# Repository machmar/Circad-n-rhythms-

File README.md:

# Circad-n-rhythms-

Sadly, this project has stalled and while I have plans to make it much better in the future, there so far is no date for these plans and other stuff is more important right now.    
  
If you are just seeing this module for the first time, let me introduce you to the basic concept of what it is and what it was.  
This is a eurorack module that was originally a clone of *Circadian Rhythms* by *TipTop Audio* but later on I decided to make it my own. I have rewritten the code and redisegined the PCB for it multiple times but never got into a place were the programming would get clean and straight forward. I suspect this is mostly because I coded the whole thing in one file with Arduino IDE. So if any new versions of the code ever come out, it willl be written in Microchip Studio instead.  But the Hardware, other than the noise on powerlines that it makes, is a in a good state with all the stuff nescessary for further development  
  
Anyways, all the mistakes that I am aware are now fixed and the module should be usable and responsive. the DAC is not used so it is not nescessary but if you want to you can have a go at adding the functionality, the protocol should be implemented with functions for intialization, selecting a channel and setting the voltage.

If you want to build it, or even build multiple and sell it to other people, send me an e-mail (marekmach24@gmail.com) and I'll send you the files for 3D printing like the faceplate, buttons and others (I'll also tell you what the serial number should be 🤭🤭). Advantage for doing it this way is that if you face any issues, I can help you out pretty quickly and easilly as you already have a direct line to me.  

More info here:  
Flashing guide [Here on wiki](https://github.com/machmar/Circad-n-rhythms-/wiki/)  
Video overview [on my youtube channel](https://youtu.be/im8Ey7QF54s)

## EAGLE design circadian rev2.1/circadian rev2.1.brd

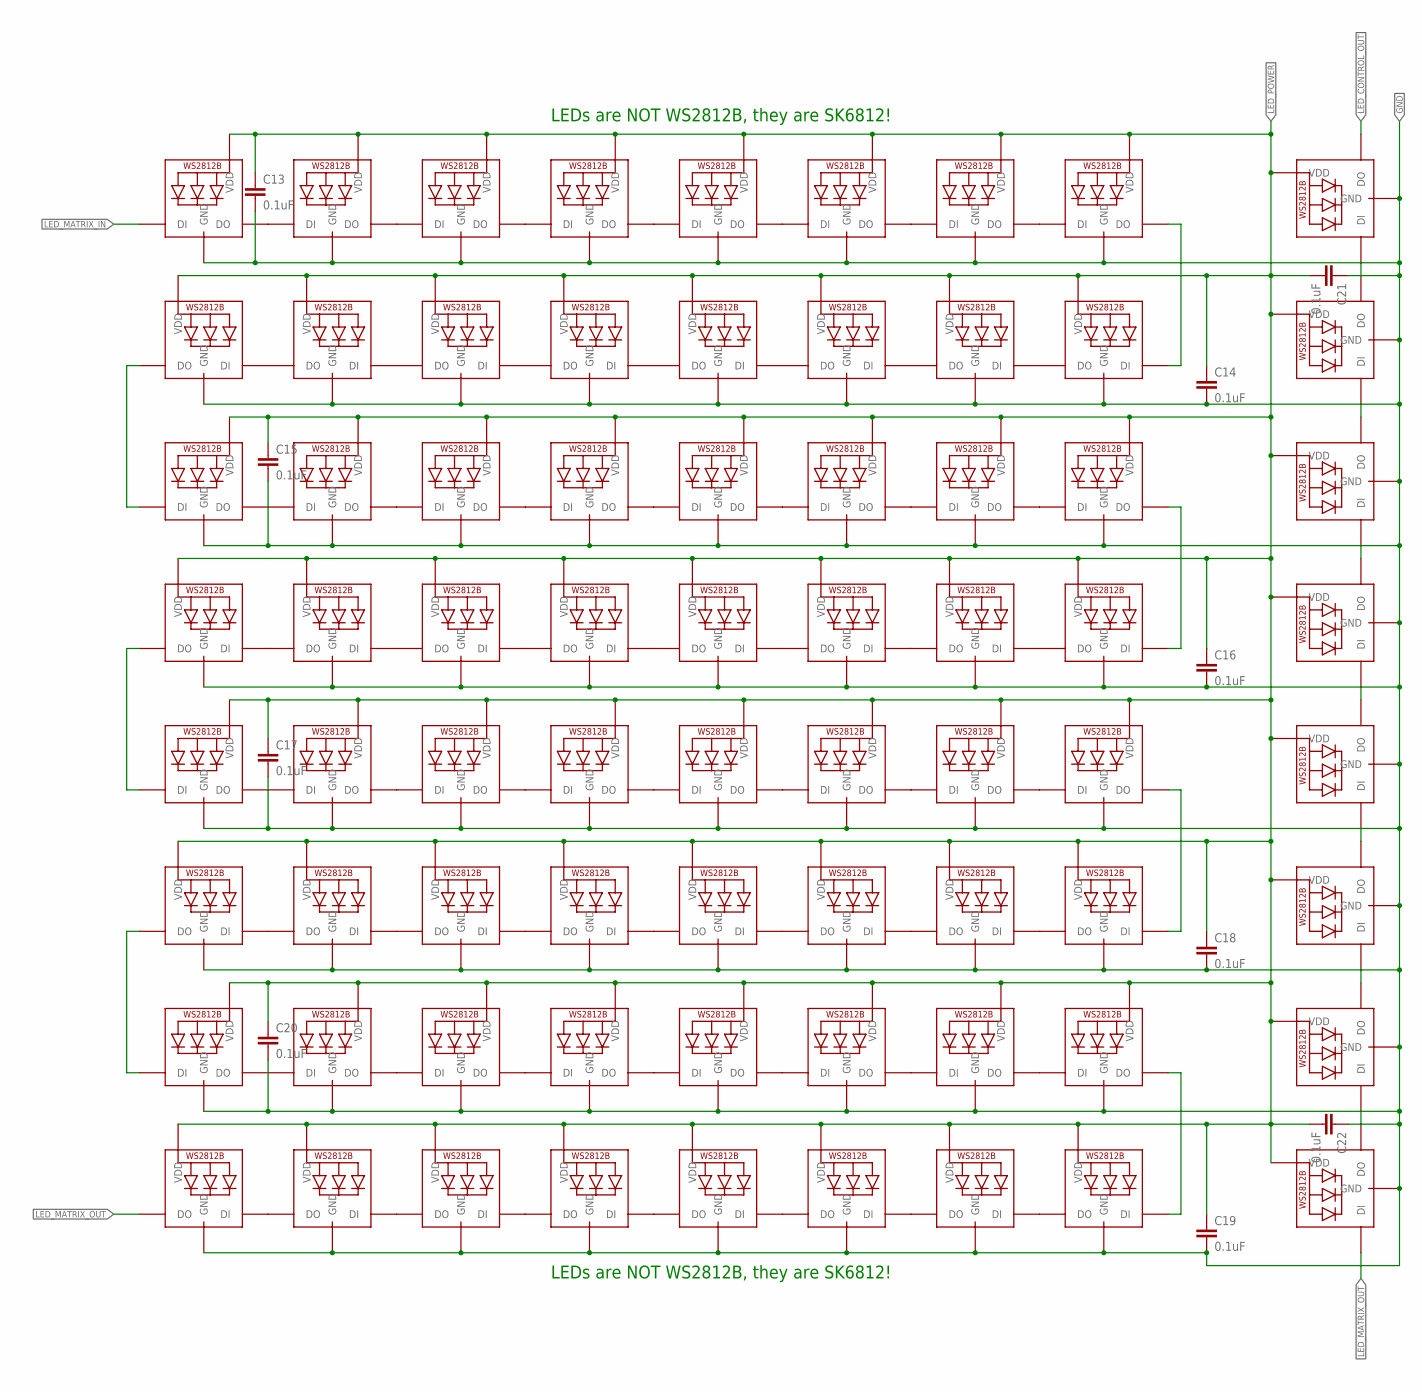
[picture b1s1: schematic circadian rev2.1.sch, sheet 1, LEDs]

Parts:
C13, C14, C15, C16, C17, C18, C19, C20, C21, C22: 0.1uF; 0603
LED1, LED2, LED3, LED4, LED5, LED6, LED7, LED8, LED9, LED10, LED11, LED12, LED13, LED14, LED15, LED16, LED17, LED18, LED19, LED20, LED21, LED22, LED23, LED24, LED25, LED26, LED27, LED28, LED29, LED30, LED31, LED32, LED33, LED34, LED35, LED36, LED37, LED38, LED39, LED40, LED41, LED42, LED43, LED44, LED45, LED46, LED47, LED48, LED49, LED50, LED51, LED52, LED53, LED54, LED55, LED56, LED57, LED58, LED59, LED60, LED61, LED62, LED63, LED64, LED65, LED66, LED67, LED68, LED69, LED70, LED71, LED72: SK68123535; LED3535

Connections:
GND: C13.2, C14.2, C15.2, C16.2, C17.2, C18.2, C19.2, C20.2, C21.1, C22.1, LED1.4 (GND), LED2.4 (GND), LED3.4 (GND), LED4.4 (GND), LED5.4 (GND), LED6.4 (GND), LED7.4 (GND), LED8.4 (GND), LED9.4 (GND), LED10.4 (GND), LED11.4 (GND), LED12.4 (GND), LED13.4 (GND), LED14.4 (GND), LED15.4 (GND), LED16.4 (GND), LED17.4 (GND), LED18.4 (GND), LED19.4 (GND), LED20.4 (GND), LED21.4 (GND), LED22.4 (GND), LED23.4 (GND), LED24.4 (GND), LED25.4 (GND), LED26.4 (GND), LED27.4 (GND), LED28.4 (GND), LED29.4 (GND), LED30.4 (GND), LED31.4 (GND), LED32.4 (GND), LED33.4 (GND), LED34.4 (GND), LED35.4 (GND), LED36.4 (GND), LED37.4 (GND), LED38.4 (GND), LED39.4 (GND), LED40.4 (GND), LED41.4 (GND), LED42.4 (GND), LED43.4 (GND), LED44.4 (GND), LED45.4 (GND), LED46.4 (GND), LED47.4 (GND), LED48.4 (GND), LED49.4 (GND), LED50.4 (GND), LED51.4 (GND), LED52.4 (GND), LED53.4 (GND), LED54.4 (GND), LED55.4 (GND), LED56.4 (GND), LED57.4 (GND), LED58.4 (GND), LED59.4 (GND), LED60.4 (GND), LED61.4 (GND), LED62.4 (GND), LED63.4 (GND), LED64.4 (GND), LED65.4 (GND), LED66.4 (GND), LED67.4 (GND), LED68.4 (GND), LED69.4 (GND), LED70.4 (GND), LED71.4 (GND), LED72.4 (GND); also elsewhere on the board
LED_CONTROL_OUT: LED65.3 (DO)
LED_MATRIX_IN: LED1.1 (DI); also elsewhere on the board
LED_MATRIX_OUT: LED64.3 (DO), LED72.1 (DI)
LED_POWER: C13.1, C14.1, C15.1, C16.1, C17.1, C18.1, C19.1, C20.1, C21.2, C22.2, LED1.2 (VDD), LED2.2 (VDD), LED3.2 (VDD), LED4.2 (VDD), LED5.2 (VDD), LED6.2 (VDD), LED7.2 (VDD), LED8.2 (VDD), LED9.2 (VDD), LED10.2 (VDD), LED11.2 (VDD), LED12.2 (VDD), LED13.2 (VDD), LED14.2 (VDD), LED15.2 (VDD), LED16.2 (VDD), LED17.2 (VDD), LED18.2 (VDD), LED19.2 (VDD), LED20.2 (VDD), LED21.2 (VDD), LED22.2 (VDD), LED23.2 (VDD), LED24.2 (VDD), LED25.2 (VDD), LED26.2 (VDD), LED27.2 (VDD), LED28.2 (VDD), LED29.2 (VDD), LED30.2 (VDD), LED31.2 (VDD), LED32.2 (VDD), LED33.2 (VDD), LED34.2 (VDD), LED35.2 (VDD), LED36.2 (VDD), LED37.2 (VDD), LED38.2 (VDD), LED39.2 (VDD), LED40.2 (VDD), LED41.2 (VDD), LED42.2 (VDD), LED43.2 (VDD), LED44.2 (VDD), LED45.2 (VDD), LED46.2 (VDD), LED47.2 (VDD), LED48.2 (VDD), LED49.2 (VDD), LED50.2 (VDD), LED51.2 (VDD), LED52.2 (VDD), LED53.2 (VDD), LED54.2 (VDD), LED55.2 (VDD), LED56.2 (VDD), LED57.2 (VDD), LED58.2 (VDD), LED59.2 (VDD), LED60.2 (VDD), LED61.2 (VDD), LED62.2 (VDD), LED63.2 (VDD), LED64.2 (VDD), LED65.2 (VDD), LED66.2 (VDD), LED67.2 (VDD), LED68.2 (VDD), LED69.2 (VDD), LED70.2 (VDD), LED71.2 (VDD), LED72.2 (VDD); also elsewhere on the board
unnamed: LED9.3 (DO), LED10.1 (DI)
unnamed: LED10.3 (DO), LED11.1 (DI)
unnamed: LED11.3 (DO), LED12.1 (DI)
unnamed: LED12.3 (DO), LED13.1 (DI)
unnamed: LED13.3 (DO), LED14.1 (DI)
unnamed: LED14.3 (DO), LED15.1 (DI)
unnamed: LED15.3 (DO), LED16.1 (DI)
unnamed: LED8.3 (DO), LED9.1 (DI)
unnamed: LED17.3 (DO), LED18.1 (DI)
unnamed: LED18.3 (DO), LED19.1 (DI)
unnamed: LED19.3 (DO), LED20.1 (DI)
unnamed: LED20.3 (DO), LED21.1 (DI)
unnamed: LED21.3 (DO), LED22.1 (DI)
unnamed: LED22.3 (DO), LED23.1 (DI)
unnamed: LED23.3 (DO), LED24.1 (DI)
unnamed: LED1.3 (DO), LED2.1 (DI)
unnamed: LED2.3 (DO), LED3.1 (DI)
unnamed: LED3.3 (DO), LED4.1 (DI)
unnamed: LED4.3 (DO), LED5.1 (DI)
unnamed: LED5.3 (DO), LED6.1 (DI)
unnamed: LED6.3 (DO), LED7.1 (DI)
unnamed: LED7.3 (DO), LED8.1 (DI)
unnamed: LED25.3 (DO), LED26.1 (DI)
unnamed: LED26.3 (DO), LED27.1 (DI)
unnamed: LED27.3 (DO), LED28.1 (DI)
unnamed: LED28.3 (DO), LED29.1 (DI)
unnamed: LED29.3 (DO), LED30.1 (DI)
unnamed: LED30.3 (DO), LED31.1 (DI)
unnamed: LED31.3 (DO), LED32.1 (DI)
unnamed: LED24.3 (DO), LED25.1 (DI)
unnamed: LED33.3 (DO), LED34.1 (DI)
unnamed: LED34.3 (DO), LED35.1 (DI)
unnamed: LED35.3 (DO), LED36.1 (DI)
unnamed: LED36.3 (DO), LED37.1 (DI)
unnamed: LED37.3 (DO), LED38.1 (DI)
unnamed: LED38.3 (DO), LED39.1 (DI)
unnamed: LED39.3 (DO), LED40.1 (DI)
unnamed: LED41.3 (DO), LED42.1 (DI)
unnamed: LED42.3 (DO), LED43.1 (DI)
unnamed: LED43.3 (DO), LED44.1 (DI)
unnamed: LED44.3 (DO), LED45.1 (DI)
unnamed: LED45.3 (DO), LED46.1 (DI)
unnamed: LED46.3 (DO), LED47.1 (DI)
unnamed: LED47.3 (DO), LED48.1 (DI)
unnamed: LED40.3 (DO), LED41.1 (DI)
unnamed: LED49.3 (DO), LED50.1 (DI)
unnamed: LED50.3 (DO), LED51.1 (DI)
unnamed: LED51.3 (DO), LED52.1 (DI)
unnamed: LED52.3 (DO), LED53.1 (DI)
unnamed: LED53.3 (DO), LED54.1 (DI)
unnamed: LED54.3 (DO), LED55.1 (DI)
unnamed: LED55.3 (DO), LED56.1 (DI)
unnamed: LED57.3 (DO), LED58.1 (DI)
unnamed: LED58.3 (DO), LED59.1 (DI)
unnamed: LED59.3 (DO), LED60.1 (DI)
unnamed: LED60.3 (DO), LED61.1 (DI)
unnamed: LED61.3 (DO), LED62.1 (DI)
unnamed: LED62.3 (DO), LED63.1 (DI)
unnamed: LED63.3 (DO), LED64.1 (DI)
unnamed: LED56.3 (DO), LED57.1 (DI)
unnamed: LED16.3 (DO), LED17.1 (DI)
unnamed: LED32.3 (DO), LED33.1 (DI)
unnamed: LED48.3 (DO), LED49.1 (DI)
unnamed: LED66.1 (DI), LED67.3 (DO)
unnamed: LED67.1 (DI), LED68.3 (DO)
unnamed: LED68.1 (DI), LED69.3 (DO)
unnamed: LED69.1 (DI), LED70.3 (DO)
unnamed: LED70.1 (DI), LED71.3 (DO)
unnamed: LED71.1 (DI), LED72.3 (DO)
unnamed: LED65.1 (DI), LED66.3 (DO)

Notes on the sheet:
LEDs are NOT WS2812B, they are SK6812!

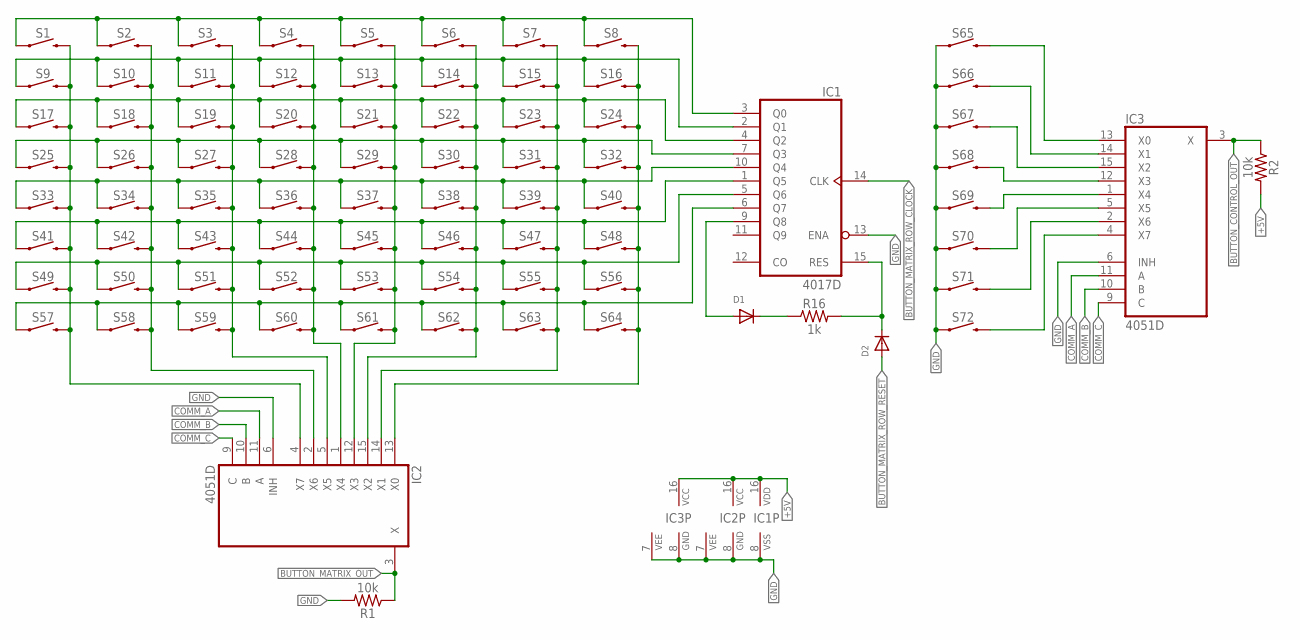
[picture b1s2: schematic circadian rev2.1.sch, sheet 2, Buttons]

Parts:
D1, D2: DIODESOD-123; SOD-123
IC1: 4017D; SO16
IC2, IC3: 4051D; SO16
R1, R2: 10k; 0603
R16: 1k; 0603
S1, S2, S3, S4, S5, S6, S7, S8, S9, S10, S11, S12, S13, S14, S15, S16, S17, S18, S19, S20, S21, S22, S23, S24, S25, S26, S27, S28, S29, S30, S31, S32, S33, S34, S35, S36, S37, S38, S39, S40, S41, S42, S43, S44, S45, S46, S47, S48, S49, S50, S51, S52, S53, S54, S55, S56, S57, S58, S59, S60, S61, S62, S63, S64, S65, S66, S67, S68, S69, S70, S71, S72: MOMENTARY-SWITCH-SPST-SMD-6.0X3.5MM; TACTILE_SWITCH_SMD_6.0X3.5MM

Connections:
+5V: IC1.16 (VDD), IC2.16 (VCC), IC3.16 (VCC), R2.2; also elsewhere on the board
BUTTON_CONTROL_OUT: IC3.3 (X), R2.1; also elsewhere on the board
BUTTON_MATRIX_COLLUM1: IC2.4 (X7), S1.2, S9.2, S17.2, S25.2, S33.2, S41.2, S49.2, S57.2
BUTTON_MATRIX_COLLUM2: IC2.2 (X6), S2.2, S10.2, S18.2, S26.2, S34.2, S42.2, S50.2, S58.2
BUTTON_MATRIX_COLLUM3: IC2.5 (X5), S3.2, S11.2, S19.2, S27.2, S35.2, S43.2, S51.2, S59.2
BUTTON_MATRIX_COLLUM4: IC2.1 (X4), S4.2, S12.2, S20.2, S28.2, S36.2, S44.2, S52.2, S60.2
BUTTON_MATRIX_COLLUM5: IC2.12 (X3), S5.2, S13.2, S21.2, S29.2, S37.2, S45.2, S53.2, S61.2
BUTTON_MATRIX_COLLUM6: IC2.15 (X2), S6.2, S14.2, S22.2, S30.2, S38.2, S46.2, S54.2, S62.2
BUTTON_MATRIX_COLLUM7: IC2.14 (X1), S7.2, S15.2, S23.2, S31.2, S39.2, S47.2, S55.2, S63.2
BUTTON_MATRIX_COLLUM8: IC2.13 (X0), S8.2, S16.2, S24.2, S32.2, S40.2, S48.2, S56.2, S64.2
BUTTON_MATRIX_OUT: IC2.3 (X), R1.1; also elsewhere on the board
BUTTON_MATRIX_ROW1: IC1.3 (Q0), S1.1, S2.1, S3.1, S4.1, S5.1, S6.1, S7.1, S8.1
BUTTON_MATRIX_ROW2: IC1.2 (Q1), S9.1, S10.1, S11.1, S12.1, S13.1, S14.1, S15.1, S16.1
BUTTON_MATRIX_ROW3: IC1.4 (Q2), S17.1, S18.1, S19.1, S20.1, S21.1, S22.1, S23.1, S24.1
BUTTON_MATRIX_ROW4: IC1.7 (Q3), S25.1, S26.1, S27.1, S28.1, S29.1, S30.1, S31.1, S32.1
BUTTON_MATRIX_ROW5: IC1.10 (Q4), S33.1, S34.1, S35.1, S36.1, S37.1, S38.1, S39.1, S40.1
BUTTON_MATRIX_ROW6: IC1.1 (Q5), S41.1, S42.1, S43.1, S44.1, S45.1, S46.1, S47.1, S48.1
BUTTON_MATRIX_ROW7: IC1.5 (Q6), S49.1, S50.1, S51.1, S52.1, S53.1, S54.1, S55.1, S56.1
BUTTON_MATRIX_ROW8: IC1.6 (Q7), S57.1, S58.1, S59.1, S60.1, S61.1, S62.1, S63.1, S64.1
BUTTON_MATRIX_ROW_CLOCK: IC1.14 (CLK); also elsewhere on the board
BUTTON_MATRIX_ROW_RESET: D2.A; also elsewhere on the board
COMM_A: IC2.11 (A), IC3.11 (A); also elsewhere on the board
COMM_B: IC2.10 (B), IC3.10 (B); also elsewhere on the board
COMM_C: IC2.9 (C), IC3.9 (C); also elsewhere on the board
GND: IC1.8 (VSS), IC1.13 (ENA), IC2.6 (INH), IC2.7 (VEE), IC2.8 (GND), IC3.6 (INH), IC3.7 (VEE), IC3.8 (GND), R1.2, S65.1, S66.1, S67.1, S68.1, S69.1, S70.1, S71.1, S72.1; also elsewhere on the board
unnamed: IC3.12 (X3), S68.2
unnamed: IC3.1 (X4), S69.2
unnamed: IC3.5 (X5), S70.2
unnamed: IC3.15 (X2), S67.2
unnamed: IC3.14 (X1), S66.2
unnamed: IC3.13 (X0), S65.2
unnamed: IC3.2 (X6), S71.2
unnamed: IC3.4 (X7), S72.2
unnamed: D1.C, R16.1
unnamed: D1.A, IC1.9 (Q8)
unnamed: D2.C, IC1.15 (RES), R16.2

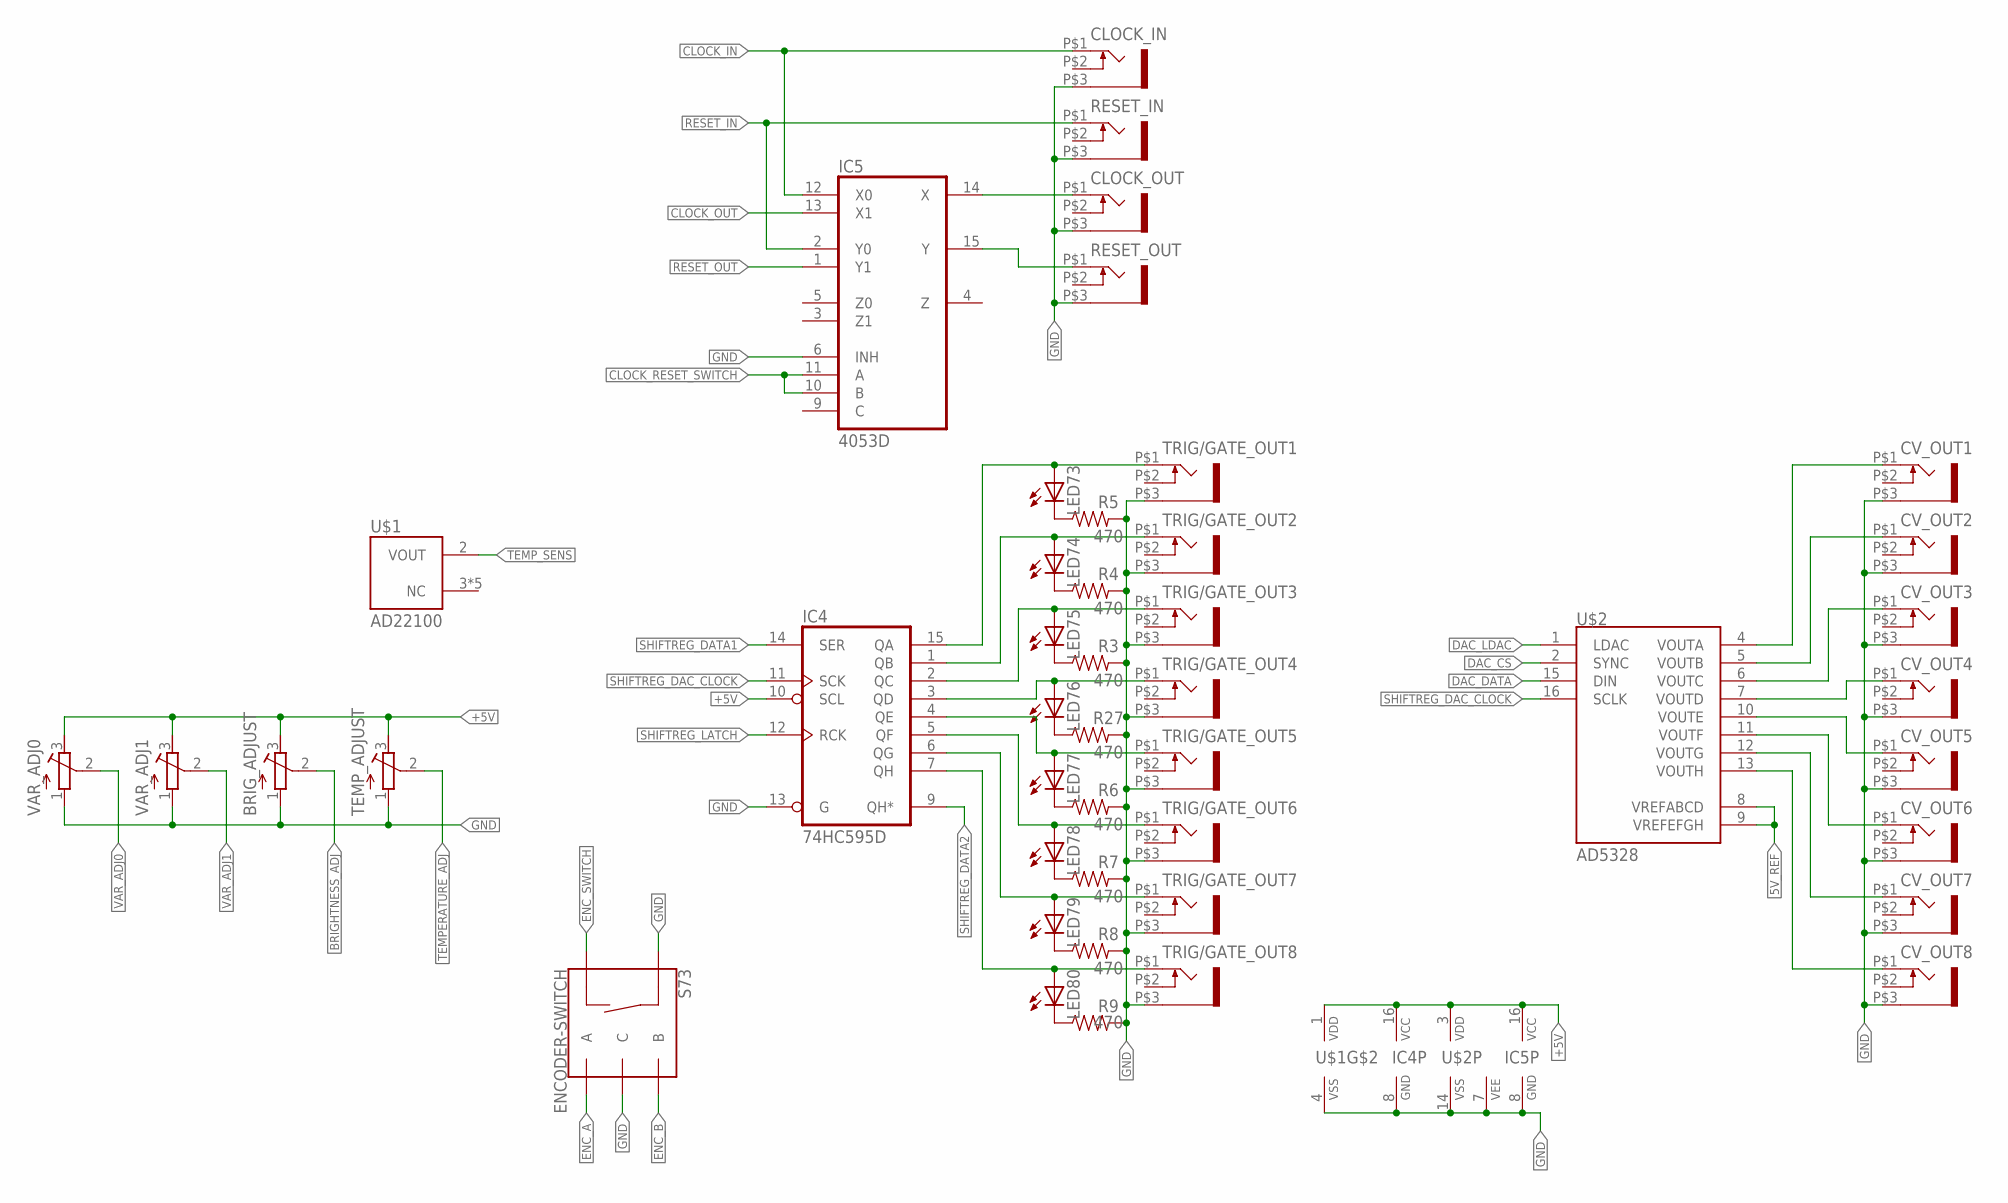
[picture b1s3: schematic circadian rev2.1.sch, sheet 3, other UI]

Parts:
BRIG_ADJUST: R-TRIMM4G/J; RTRIM4G/J
CLOCK_IN: WQP-PJ301M-12_JACK
CLOCK_OUT: WQP-PJ301M-12_JACK
CV_OUT1, CV_OUT2, CV_OUT3, CV_OUT4, CV_OUT5, CV_OUT6, CV_OUT7, CV_OUT8: WQP-PJ301M-12_JACK
IC4: 74HC595D; SO16
IC5: 4053D; SO16
LED73, LED74, LED75, LED76, LED77, LED78, LED79, LED80: LED5MM
R3, R4, R5, R6, R7, R8, R9, R27: 470; 0603
RESET_IN: WQP-PJ301M-12_JACK
RESET_OUT: WQP-PJ301M-12_JACK
S73: ENCODER-SWITCH; ROTARY_ENC_PLAIN
TEMP_ADJUST: R-TRIMM4G/J; RTRIM4G/J
TRIG/GATE_OUT1, TRIG/GATE_OUT2, TRIG/GATE_OUT3, TRIG/GATE_OUT4, TRIG/GATE_OUT5, TRIG/GATE_OUT6, TRIG/GATE_OUT7, TRIG/GATE_OUT8: WQP-PJ301M-12_JACK
U$1: AD22100; SO08
U$2: AD5328; TSSOP-16
VAR_ADJ0, VAR_ADJ1: R-TRIMM4G/J; RTRIM4G/J

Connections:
5V_REF: U$2.8 (VREFABCD), U$2.9 (VREFEFGH); also elsewhere on the board
+5V: BRIG_ADJUST.3 (E), IC4.10 (SCL), IC4.16 (VCC), IC5.16 (VCC), TEMP_ADJUST.3 (E), U$1.1 (VDD), U$2.3 (VDD), VAR_ADJ0.3 (E), VAR_ADJ1.3 (E); also elsewhere on the board
BRIGHTNESS_ADJ: BRIG_ADJUST.2 (S); also elsewhere on the board
CLOCK_IN: CLOCK_IN.P$1 (2), IC5.12 (X0); also elsewhere on the board
CLOCK_OUT: IC5.13 (X1); also elsewhere on the board
CLOCK_RESET_SWITCH: IC5.10 (B), IC5.11 (A); also elsewhere on the board
DAC_CS: U$2.2 (SYNC); also elsewhere on the board
DAC_DATA: U$2.15 (DIN); also elsewhere on the board
DAC_LDAC: U$2.1 (LDAC); also elsewhere on the board
ENC_A: S73.A; also elsewhere on the board
ENC_B: S73.B; also elsewhere on the board
ENC_SWITCH: S73.SW-; also elsewhere on the board
GND: BRIG_ADJUST.1 (A), CLOCK_IN.P$3 (1), CLOCK_OUT.P$3 (1), CV_OUT1.P$3 (1), CV_OUT2.P$3 (1), CV_OUT3.P$3 (1), CV_OUT4.P$3 (1), CV_OUT5.P$3 (1), CV_OUT6.P$3 (1), CV_OUT7.P$3 (1), CV_OUT8.P$3 (1), IC4.8 (GND), IC4.13 (G), IC5.6 (INH), IC5.7 (VEE), IC5.8 (GND), R3.2, R4.2, R5.2, R6.2, R7.2, R8.2, R9.2, R27.2, RESET_IN.P$3 (1), RESET_OUT.P$3 (1), S73.C, S73.SW+, TEMP_ADJUST.1 (A), TRIG/GATE_OUT1.P$3 (1), TRIG/GATE_OUT2.P$3 (1), TRIG/GATE_OUT3.P$3 (1), TRIG/GATE_OUT4.P$3 (1), TRIG/GATE_OUT5.P$3 (1), TRIG/GATE_OUT6.P$3 (1), TRIG/GATE_OUT7.P$3 (1), TRIG/GATE_OUT8.P$3 (1), U$1.4 (VSS), U$2.14 (VSS), VAR_ADJ0.1 (A), VAR_ADJ1.1 (A); also elsewhere on the board
unnamed: IC4.4 (QE), LED77.A, TRIG/GATE_OUT5.P$1 (2)
unnamed: IC4.3 (QD), LED76.A, TRIG/GATE_OUT4.P$1 (2)
unnamed: IC4.5 (QF), LED78.A, TRIG/GATE_OUT6.P$1 (2)
unnamed: IC4.6 (QG), LED79.A, TRIG/GATE_OUT7.P$1 (2)
unnamed: IC4.7 (QH), LED80.A, TRIG/GATE_OUT8.P$1 (2)
unnamed: IC4.2 (QC), LED75.A, TRIG/GATE_OUT3.P$1 (2)
unnamed: IC4.1 (QB), LED74.A, TRIG/GATE_OUT2.P$1 (2)
unnamed: IC4.15 (QA), LED73.A, TRIG/GATE_OUT1.P$1 (2)
unnamed: CV_OUT4.P$1 (2), U$2.7 (VOUTD)
unnamed: CV_OUT5.P$1 (2), U$2.10 (VOUTE)
unnamed: CV_OUT6.P$1 (2), U$2.11 (VOUTF)
unnamed: CV_OUT7.P$1 (2), U$2.12 (VOUTG)
unnamed: CV_OUT8.P$1 (2), U$2.13 (VOUTH)
unnamed: CV_OUT3.P$1 (2), U$2.6 (VOUTC)
unnamed: CV_OUT2.P$1 (2), U$2.5 (VOUTB)
unnamed: CV_OUT1.P$1 (2), U$2.4 (VOUTA)
unnamed: CLOCK_OUT.P$1 (2), IC5.14 (X)
unnamed: IC5.15 (Y), RESET_OUT.P$1 (2)
unnamed: LED76.K (C), R27.1
unnamed: LED75.K (C), R3.1
unnamed: LED74.K (C), R4.1
unnamed: LED73.K (C), R5.1
unnamed: LED77.K (C), R6.1
unnamed: LED78.K (C), R7.1
unnamed: LED79.K (C), R8.1
unnamed: LED80.K (C), R9.1
RESET_IN: IC5.2 (Y0), RESET_IN.P$1 (2); also elsewhere on the board
RESET_OUT: IC5.1 (Y1); also elsewhere on the board
SHIFTREG_DAC_CLOCK: IC4.11 (SCK), U$2.16 (SCLK); also elsewhere on the board
SHIFTREG_DATA1: IC4.14 (SER); also elsewhere on the board
SHIFTREG_DATA2: IC4.9 (QH*)
SHIFTREG_LATCH: IC4.12 (RCK); also elsewhere on the board
TEMPERATURE_ADJ: TEMP_ADJUST.2 (S); also elsewhere on the board
TEMP_SENS: U$1.2 (VOUT); also elsewhere on the board
VAR_ADJ0: VAR_ADJ0.2 (S); also elsewhere on the board
VAR_ADJ1: VAR_ADJ1.2 (S); also elsewhere on the board

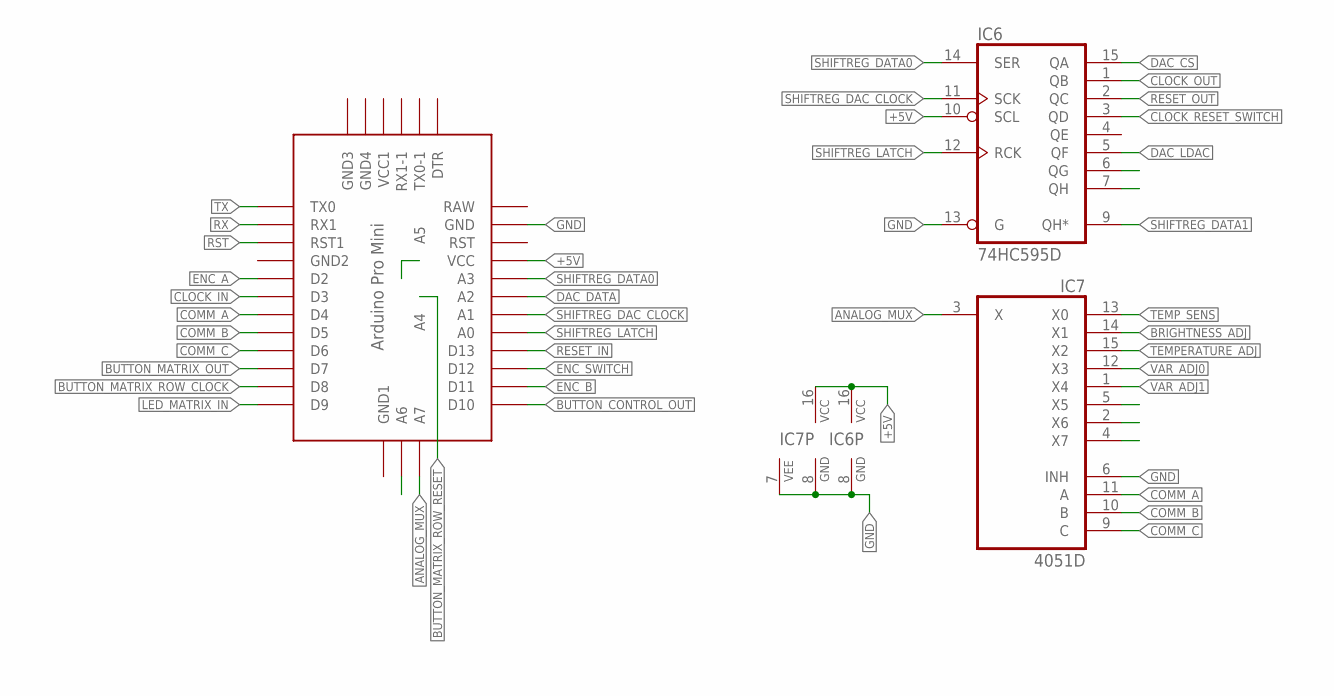
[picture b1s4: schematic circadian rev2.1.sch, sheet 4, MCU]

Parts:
IC6: 74HC595D; SO16
IC7: 4051D; SO16
U$3: ABK-PRO-MINI

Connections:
+5V: IC6.10 (SCL), IC6.16 (VCC), IC7.16 (VCC), U$3.VCC; also elsewhere on the board
ANALOG_MUX: IC7.3 (X), U$3.A7
BRIGHTNESS_ADJ: IC7.14 (X1); also elsewhere on the board
BUTTON_CONTROL_OUT: U$3.D10; also elsewhere on the board
BUTTON_MATRIX_OUT: U$3.D7; also elsewhere on the board
BUTTON_MATRIX_ROW_CLOCK: U$3.D8; also elsewhere on the board
BUTTON_MATRIX_ROW_RESET: U$3.A4; also elsewhere on the board
CLOCK_IN: U$3.D3; also elsewhere on the board
CLOCK_OUT: IC6.1 (QB); also elsewhere on the board
CLOCK_RESET_SWITCH: IC6.3 (QD); also elsewhere on the board
COMM_A: IC7.11 (A), U$3.D4; also elsewhere on the board
COMM_B: IC7.10 (B), U$3.D5; also elsewhere on the board
COMM_C: IC7.9 (C), U$3.D6; also elsewhere on the board
DAC_CS: IC6.15 (QA); also elsewhere on the board
DAC_DATA: U$3.A2; also elsewhere on the board
DAC_LDAC: IC6.5 (QF); also elsewhere on the board
ENC_A: U$3.D2; also elsewhere on the board
ENC_B: U$3.D11; also elsewhere on the board
ENC_SWITCH: U$3.D12; also elsewhere on the board
GND: IC6.8 (GND), IC6.13 (G), IC7.6 (INH), IC7.7 (VEE), IC7.8 (GND), U$3.GND; also elsewhere on the board
LED_MATRIX_IN: U$3.D9; also elsewhere on the board
RESET_IN: U$3.D13; also elsewhere on the board
RESET_OUT: IC6.2 (QC); also elsewhere on the board
RST: U$3.RST1; also elsewhere on the board
RX: U$3.RX1; also elsewhere on the board
SHIFTREG_DAC_CLOCK: IC6.11 (SCK), U$3.A1; also elsewhere on the board
SHIFTREG_DATA0: IC6.14 (SER), U$3.A3
SHIFTREG_DATA1: IC6.9 (QH*); also elsewhere on the board
SHIFTREG_LATCH: IC6.12 (RCK), U$3.A0; also elsewhere on the board
TEMPERATURE_ADJ: IC7.15 (X2); also elsewhere on the board
TEMP_SENS: IC7.13 (X0); also elsewhere on the board
TX: U$3.TX0; also elsewhere on the board
VAR_ADJ0: IC7.12 (X3); also elsewhere on the board
VAR_ADJ1: IC7.1 (X4); also elsewhere on the board

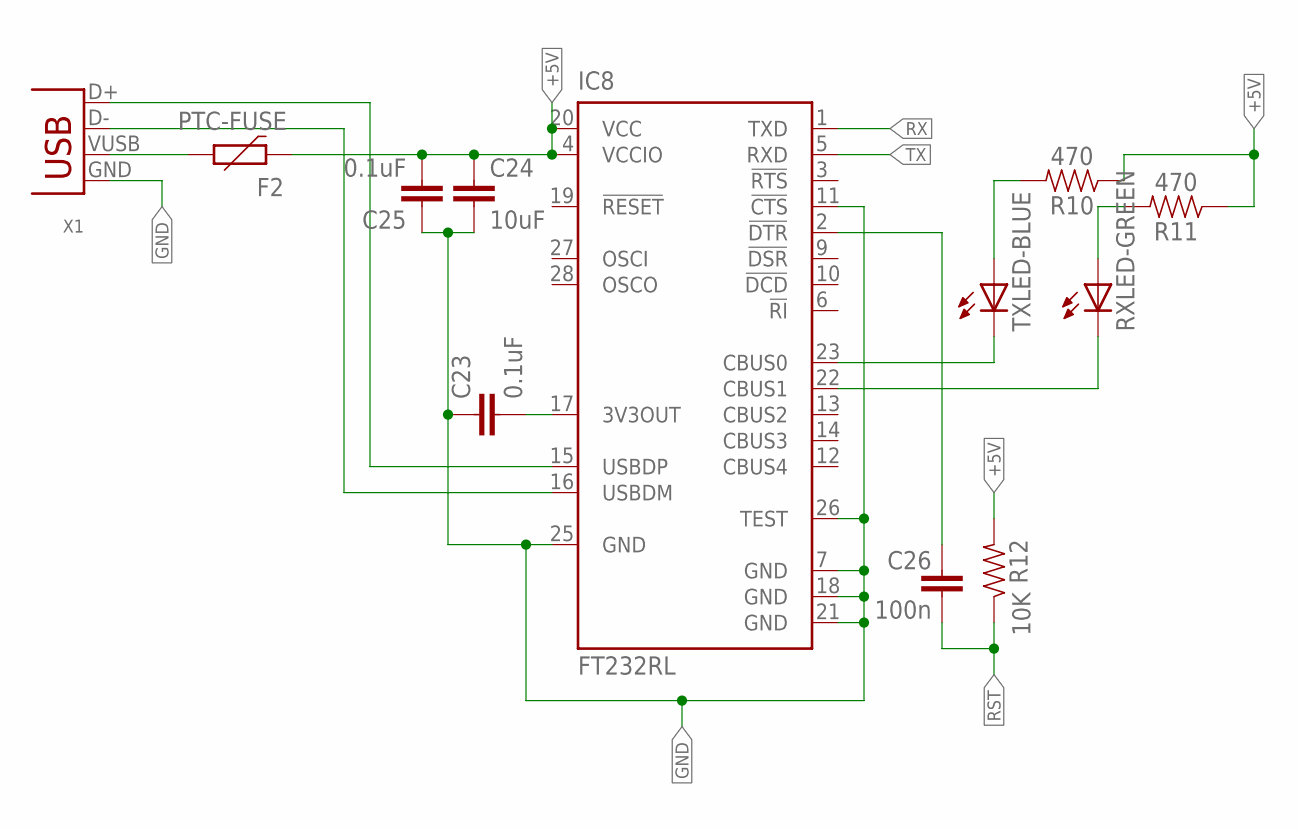
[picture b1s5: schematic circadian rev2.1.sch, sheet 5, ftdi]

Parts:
C23, C25: 0.1uF; 0603
C24: 10uF; 0603
C26: 100n; 0603-CAP
F2: PTC-FUSE; 1206
IC8: FT232RL; SSOP28
R10, R11: 470; 0603
R12: 10K; 0603-RES
RXLED-GREEN: LEDCHIP-LED0603; CHIP-LED0603
TXLED-BLUE: LEDCHIP-LED0603; CHIP-LED0603
X1: USB-B-S; USB-B-SMT

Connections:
+5V: C24.1, C25.2, F2.1, IC8.4 (VCCIO), IC8.20 (VCC), R10.1, R11.1, R12.2; also elsewhere on the board
DTR: C26.2, IC8.2 (!DTR)
GND: C23.1, C24.2, C25.1, IC8.7 (GND), IC8.11 (!CTS), IC8.18 (GND), IC8.21 (GND), IC8.25 (GND), IC8.26 (TEST), X1.GND; also elsewhere on the board
unnamed: R10.2, TXLED-BLUE.A
unnamed: R11.2, RXLED-GREEN.A
unnamed: IC8.23 (CBUS0), TXLED-BLUE.C
unnamed: IC8.22 (CBUS1), RXLED-GREEN.C
unnamed: F2.2, X1.VUSB (VBUS)
unnamed: IC8.15 (USBDP), X1.D+
unnamed: IC8.16 (USBDM), X1.D-
unnamed: C23.2, IC8.17 (3V3OUT)
RST: C26.1, R12.1; also elsewhere on the board
RX: IC8.1 (TXD); also elsewhere on the board
TX: IC8.5 (RXD); also elsewhere on the board

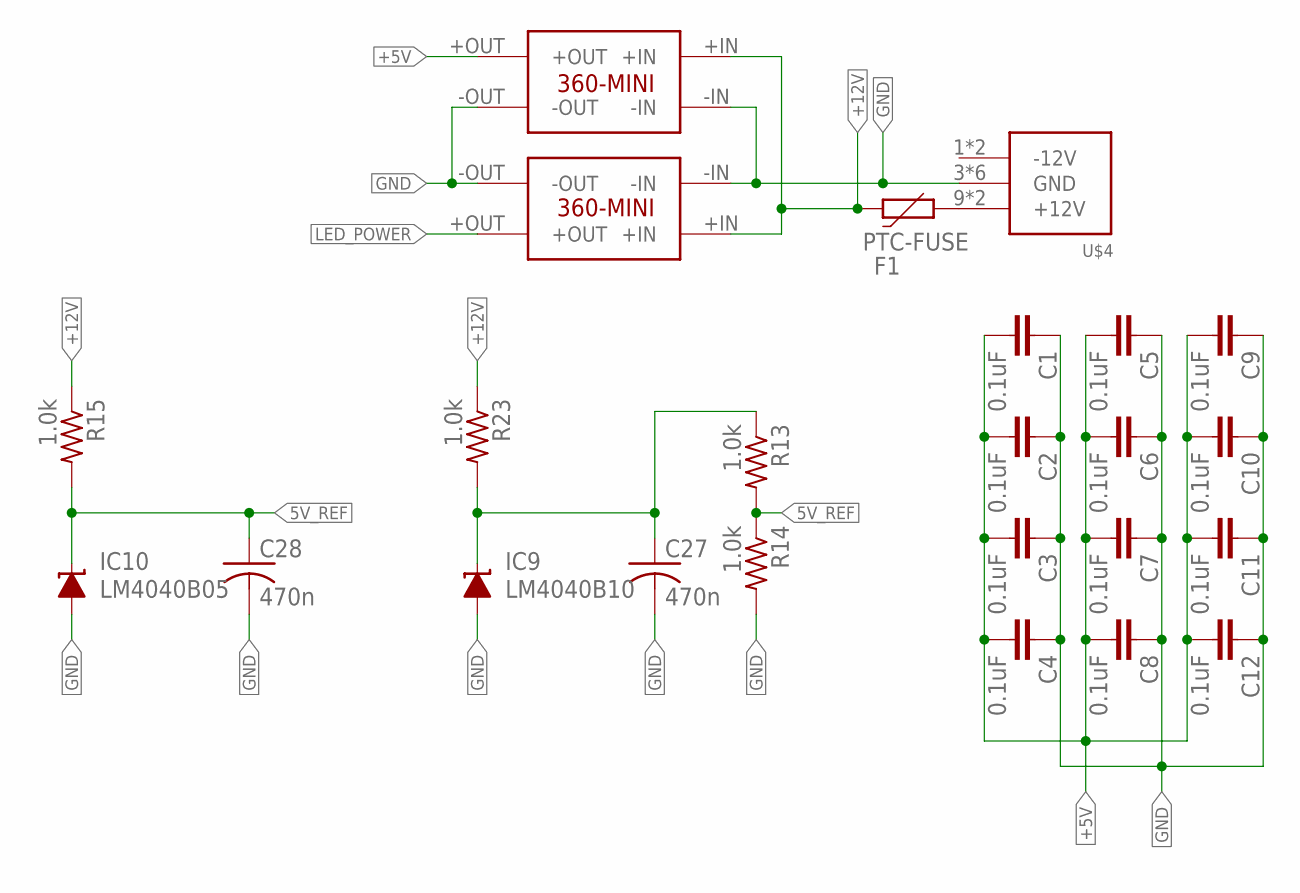
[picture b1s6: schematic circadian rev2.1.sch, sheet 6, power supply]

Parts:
C1, C2, C3, C4, C5, C6, C7, C8, C9, C10, C11, C12: 0.1uF; 0603
C27, C28: 470n; C0603
F1: PTC-FUSE; 1206
IC9: LM4040B10; DBZ_R-PDSO-G3
IC10: LM4040B05; DBZ_R-PDSO-G3
R13, R14, R15, R23: 1.0k; R0603
U$4: POWER_SIMPLE10; POWER_10
U$5, U$6: MINI-360SMD

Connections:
5V_REF: C28.1, IC10.1 (C), R13.2, R14.1, R15.2; also elsewhere on the board
+5V: C1.2, C2.2, C3.2, C4.2, C5.2, C6.2, C7.2, C8.2, C9.2, C10.2, C11.2, C12.2, U$6.+OUT; also elsewhere on the board
+12V: F1.1, R15.1, R23.1, U$5.+IN, U$6.+IN
AREF: C27.1, IC9.1 (C), R13.1, R23.2
GND: C1.1, C2.1, C3.1, C4.1, C5.1, C6.1, C7.1, C8.1, C9.1, C10.1, C11.1, C12.1, C27.2, C28.2, IC9.2 (A), IC10.2 (A), R14.2, U$4.3 (GND), U$4.4 (GND), U$4.5 (GND), U$4.6 (GND), U$4.7 (GND), U$4.8 (GND), U$5.-IN, U$5.-OUT, U$6.-IN, U$6.-OUT; also elsewhere on the board
LED_POWER: U$5.+OUT; also elsewhere on the board
unnamed: F1.2, U$4.9 (+12V), U$4.10 (+12V)

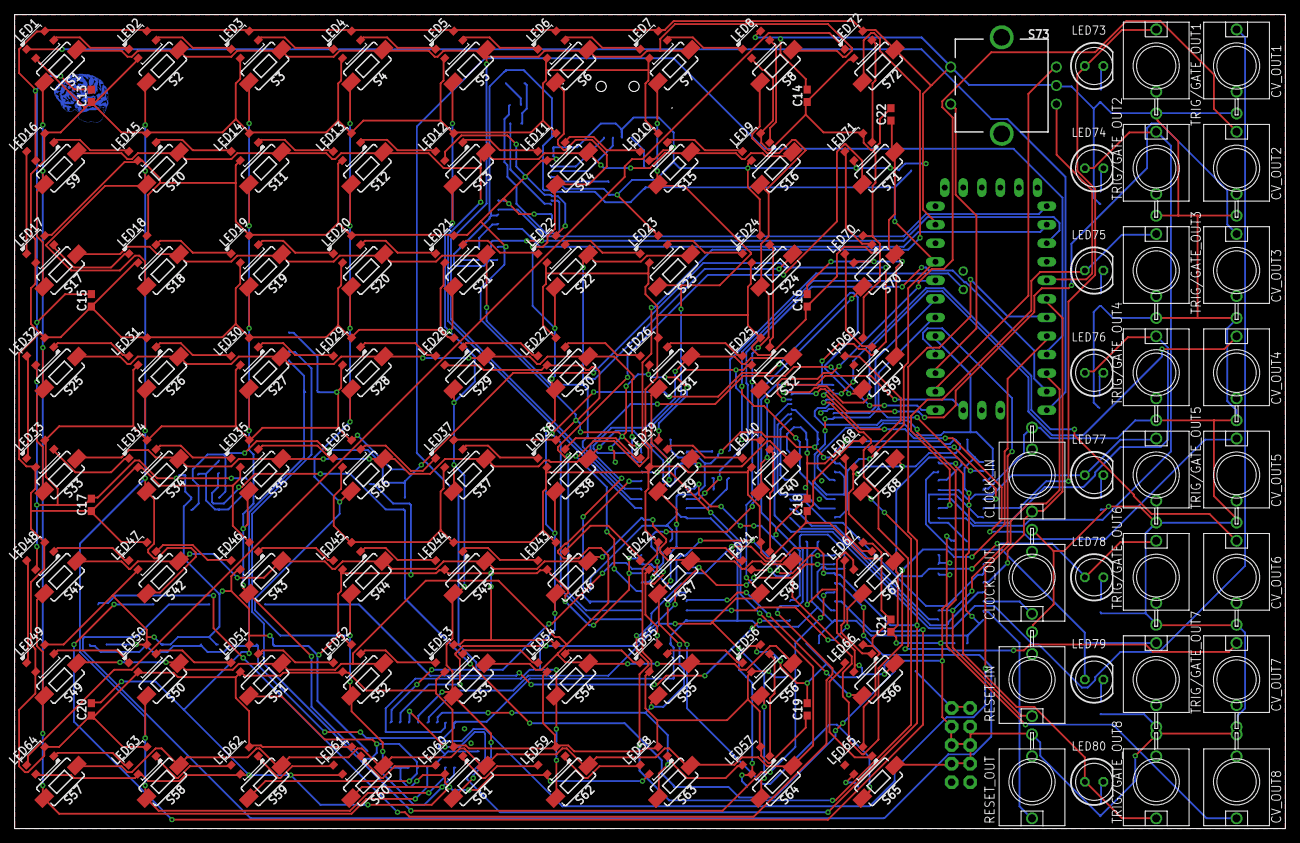
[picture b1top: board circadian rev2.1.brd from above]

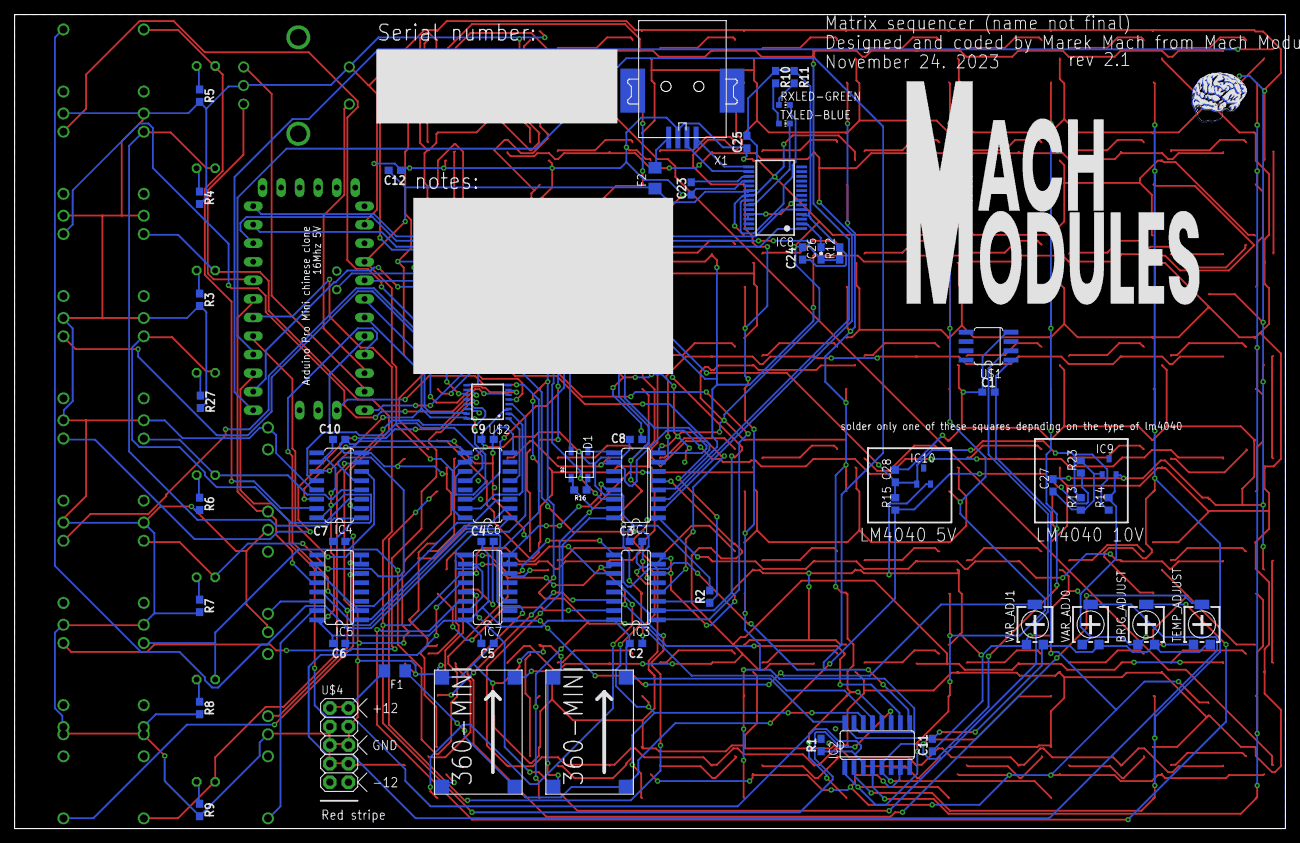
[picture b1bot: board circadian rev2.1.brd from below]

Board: 2 copper layers, 174.0 x 111.4 mm, 246 parts (63 on the bottom side), 172 nets.

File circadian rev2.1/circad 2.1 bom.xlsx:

Circad rev2.1
Index | Qty | Description | Specs | Value | Package | References
SMT parts, top side
LED1 - LED72 | 72 | SK6812 3535 (chip inside must be facing side with no leads - up on the PCB) |  |  | 3535 | SK6812 3535 RGB LED
S1 - S72 | 72 | MOMENTARY-SWITCH-SMD-6.0X3.5MM | red |  | 6.0x3.5mm | MOMENTARY-SWITCH-SMD-6.0X3.5MM
C13 - C22 | 10 | capacitor |  | 100n | 603
SMT parts, bottom side
R1, R2, R12 | 3 | resistor |  | 10k | 603
R3 - R11, R27 | 10 | resistor |  | 470 | 603
R13 - R16, R23 | 5 | resistor |  | 1k | 603
C24 | 1 | capacitor |  | 10uF | 603
C1 - C12, C23,C25, C26 | 14 | capacitor |  | 100n | 603
C27, C28 | 2 | capacitor |  | 470n | 603
D1, D2 | 2 | diode |  |  | SOD-123
F1, F2 | 2 | fuse |  | 2A | 1206
RXLED_GREEN | 1 | LED | green |  | 603
TXLED_BLUE | 1 | LED | blue |  | 603
X1 | 1 | USB B 2.0 |  |  |  | 806-KUSBX-SMTBS1NB30
VAR_ADJ0, VAR_ADJ1, TEMP_ADJUST, BRIG_ADJUST | 4 | trimmer |  | 10k | 3x3 | Trimpot SMD 3X3
IC9 USE ONLY IC9 OR IC10, NOT BOTH! | 1 | zener diode | LM4040B10 | 10V | SOT-23
IC10 USE ONLY IC9 OR IC10, NOT BOTH! | 1 | zener diode | LM4040B05 | 5V | SOT-23
IC4, IC6 | 2 | shift register | 74HC595D |  | SO16
IC2, IC3, IC7 | 2 | multiplexer | 4051D |  | SO16
IC1 | 1 | decade counter | 4017D |  | SO16
IC5 | 1 | multiplexer | 4053D |  | SO16
IC8 | 1 | usb to serial converter | FT232RL |  | SSOP28
U$1 | 1 | temperature sensor | AD22100 |  | SO08
U$2 | 1 | digital analog converter | AD5328 |  | TSSOP16
U$5, U$6 | 2 | pwm voltage regulator | MINI-360 |  |  | Mini-360 Model Step-down Module
PTH parts, top side
LED73 - LED80 | 8 | 5mm LED | red |  | 5mm | generic 5mm red LED
CLOCK_IN, CLOCK_OUT, CV_OUT1 - CV_OUT8, TRIG/GATE_OUT1 - TRIG/GATE_OUT8, RESET_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 | 20 | Vertical stereo jack connector |  |  |  | PJ366ST
S73 | 1 | rotary encoder w/ button (D shaft) |  |  |  | 688-EC11E18244A5
PTH parts, bottom side
U$4 | 1 | 2x5, 2.54mm pitch male header
Arduino pro mini chinese clone | 1 | Arduino pro mini Atmega 328pu | 16MHz 5V |  |  | Arduino pro mini Atmega 328pu 16MHz 5V
PCB specifications
PCB |  | 173.97mm x 111.43mm ; 2 layers
 | 244

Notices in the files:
parts and their libraries:
SparkFun-Capacitors: Licensing: Creative Commons ShareAlike 4.0 International - https://creativecommons.org/licenses/by-sa/4.0
